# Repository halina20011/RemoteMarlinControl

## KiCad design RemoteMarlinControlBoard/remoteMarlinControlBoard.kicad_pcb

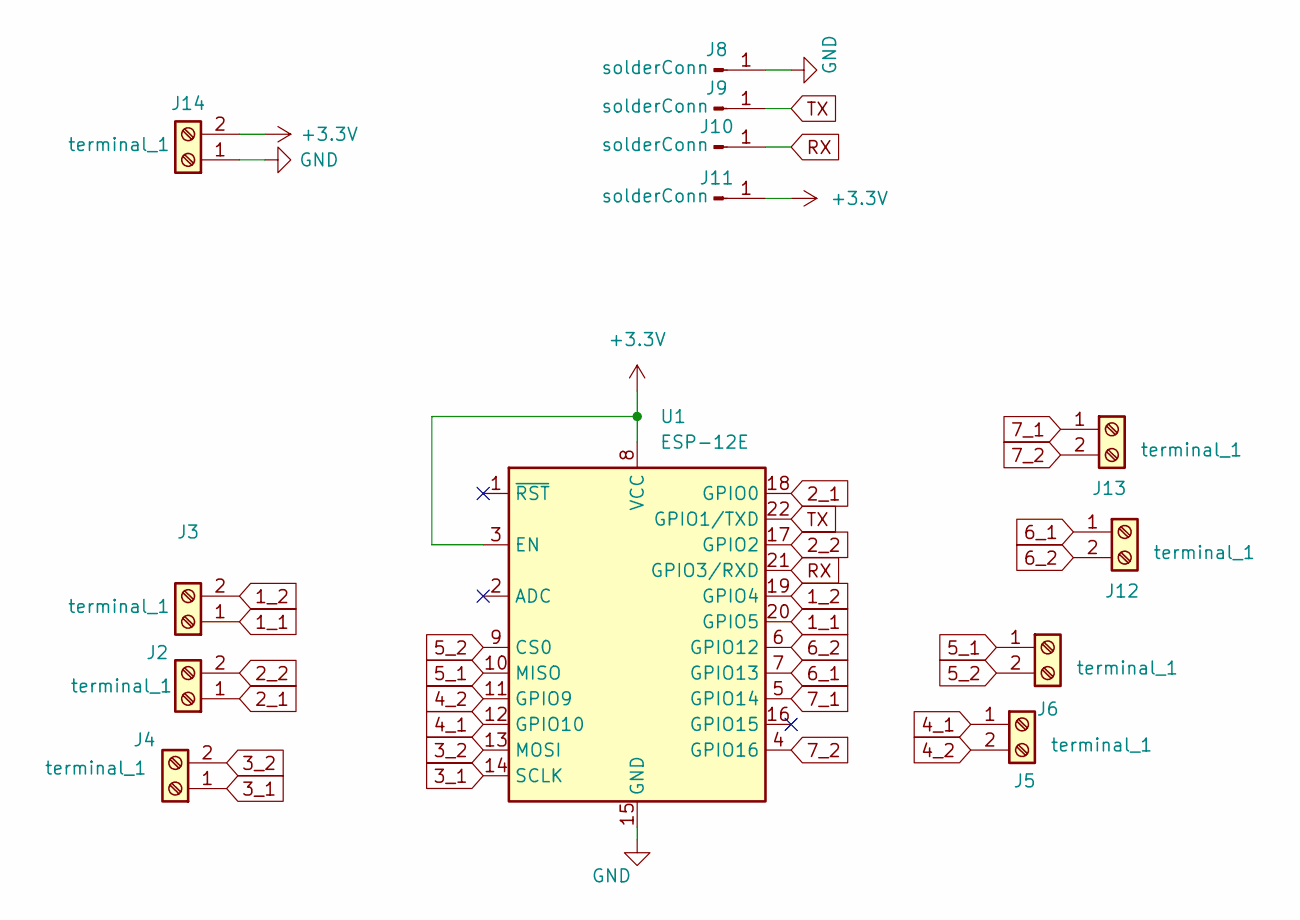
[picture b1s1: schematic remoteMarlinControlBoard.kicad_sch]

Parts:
J2, J3, J4, J5, J6, J12, J13, J14: terminal_1; TerminalBlock_MetzConnect_Type059_RT06302HBWC_1x02_P3.50mm_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
J8, J9, J10, J11: solderConn; solderConnector3
U1: ESP-12E

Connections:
1_1: J3.1, U1.20 (GPIO5)
1_2: J3.2, U1.19 (GPIO4)
2_1: J2.1, U1.18 (GPIO0)
2_2: J2.2, U1.17 (GPIO2)
3_1: J4.1, U1.14 (SCLK)
3_2: J4.2, U1.13 (MOSI)
4_1: J5.1, U1.12 (GPIO10)
4_2: J5.2, U1.11 (GPIO9)
5_1: J6.1, U1.10 (MISO)
5_2: J6.2, U1.9 (CS0)
6_1: J12.1, U1.7 (GPIO13)
6_2: J12.2, U1.6 (GPIO12)
7_1: J13.1, U1.5 (GPIO14)
7_2: J13.2, U1.4 (GPIO16)
+3.3V: J11.1, J14.2, U1.3 (EN), U1.8 (VCC)
GND: J8.1, J14.1, U1.15 (GND)
RX: J10.1, U1.21 (GPIO3/RXD)
TX: J9.1, U1.22 (GPIO1/TXD)

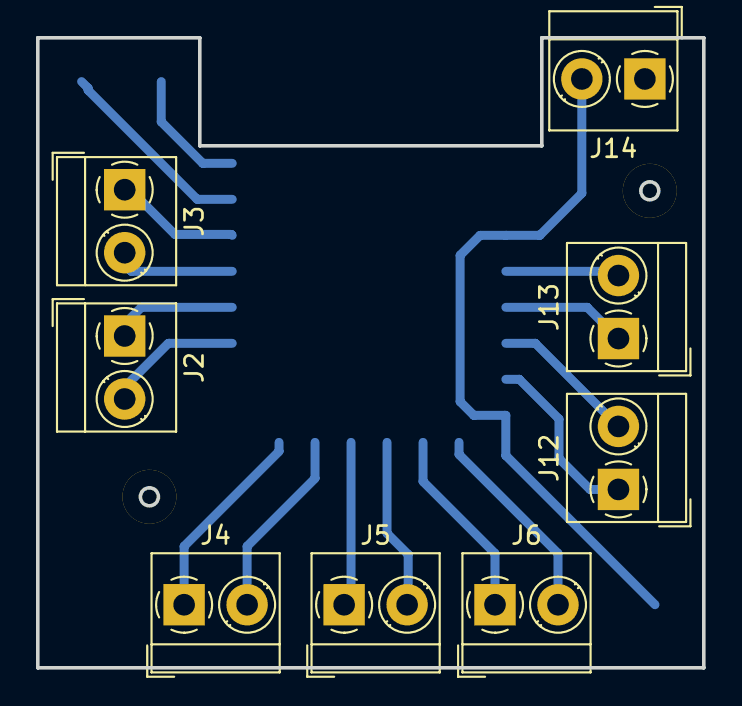
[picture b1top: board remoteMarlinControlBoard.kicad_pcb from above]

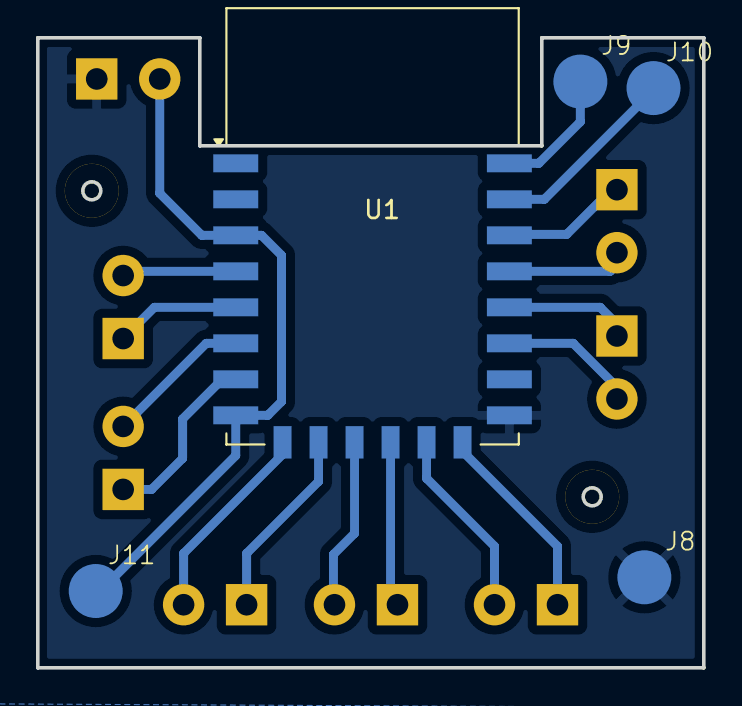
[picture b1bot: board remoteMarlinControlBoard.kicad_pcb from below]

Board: 2 copper layers, 37.0 x 35.0 mm, 15 parts (5 on the bottom side), 18 nets.

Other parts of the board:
H**: hole-3.0mm
H**#2: hole-3.0mm
